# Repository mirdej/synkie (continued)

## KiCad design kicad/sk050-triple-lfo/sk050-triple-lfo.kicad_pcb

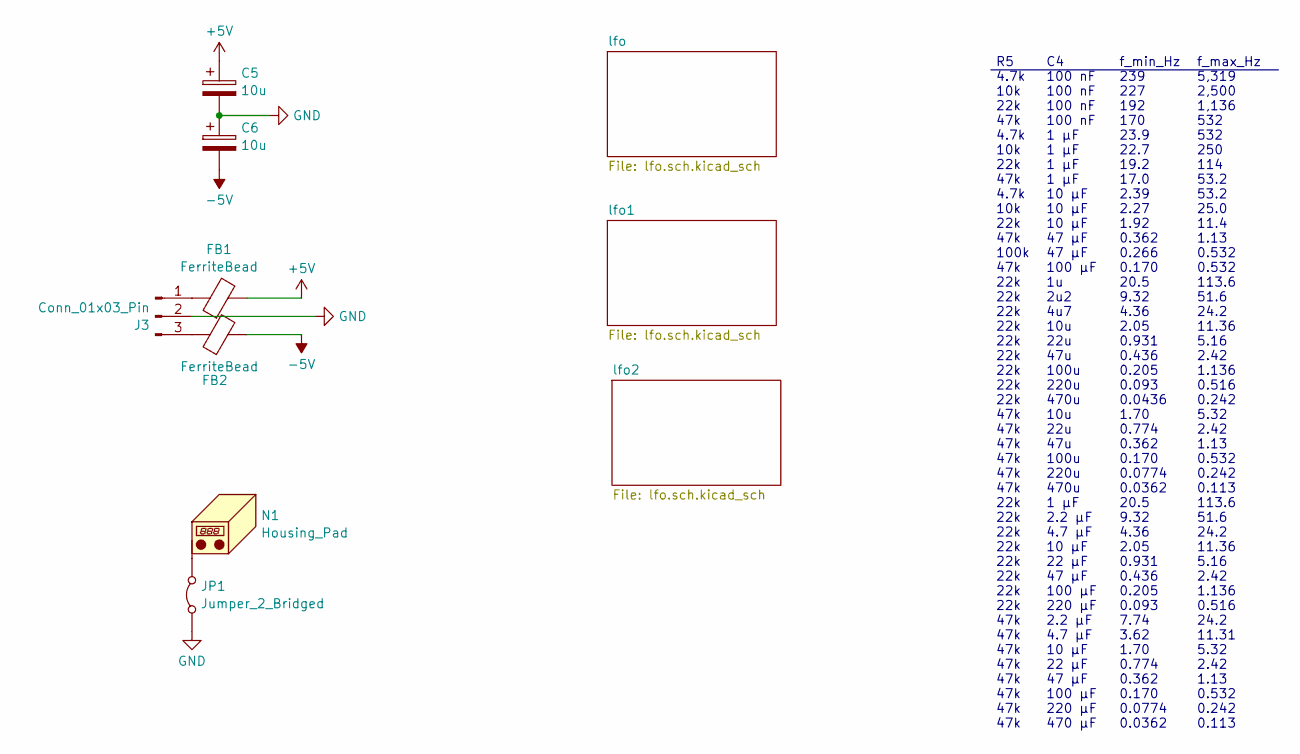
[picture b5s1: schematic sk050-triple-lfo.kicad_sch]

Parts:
C5, C6: 10u; C_0805_2012Metric; LCSC C15850
FB1, FB2: FerriteBead; L_0805_2012Metric_Pad1.15x1.40mm_HandSolder; LCSC C1017
J3: Conn_01x03_Pin; Molex_KK-254_AE-6410-03A_1x03_P2.54mm_Vertical_SMD
JP1: Jumper_2_Bridged; SolderJumper-2_P1.3mm_Bridged2Bar_Pad1.0x1.5mm
N1: Housing_Pad; Frontplate_20mm

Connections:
+5V: C5.1, FB1.2; also elsewhere on the board
-5V: C6.2, FB2.2; also elsewhere on the board
GND: C5.2, C6.1, J3.2, JP1.1 (A); also elsewhere on the board
unnamed: FB1.1, J3.1
unnamed: FB2.1, J3.3
unnamed: JP1.2 (B), N1.1 (PAD)

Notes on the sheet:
R5 4.7k 10k 22k 47k 4.7k 10k 22k 47k 4.7k 10k 22k 47k 100k 47k 22k 22k 22k 22k 22k 22k 22k 22k 22k 47k 47k 47k 47k 47k 47k 22k 22k 22k 22k 22k 22k 22k 22k 47k 47k 47k 47k 47k 47k 47k 47k
f_max_Hz 5,319 2,500 1,136 532 532 250 114 53.2 53.2 25.0 11.4 1.13 0.532 0.532 113.6 51.6 24.2 11.36 5.16 2.42 1.136 0.516 0.242 5.32 2.42 1.13 0.532 0.242 0.113 113.6 51.6 24.2 11.36 5.16 2.42 1.136 0.516 24.2 11.31 5.32 2.42 1.13 0.532 0.242 0.113
f_min_Hz 239 227 192 170 23.9 22.7 19.2 17.0 2.39 2.27 1.92 0.362 0.266 0.170 20.5 9.32 4.36 2.05 0.931 0.436 0.205 0.093 0.0436 1.70 0.774 0.362 0.170 0.0774 0.0362 20.5 9.32 4.36 2.05 0.931 0.436 0.205 0.093 7.74 3.62 1.70 0.774 0.362 0.170 0.0774 0.0362
C4 100 nF 100 nF 100 nF 100 nF 1 µF 1 µF 1 µF 1 µF 10 µF 10 µF 10 µF 47 µF 47 µF 100 µF 1u 2u2 4u7 10u 22u 47u 100u 220u 470u 10u 22u 47u 100u 220u 470u 1 µF 2.2 µF 4.7 µF 10 µF 22 µF 47 µF 100 µF 220 µF 2.2 µF 4.7 µF 10 µF 22 µF 47 µF 100 µF 220 µF 470 µF

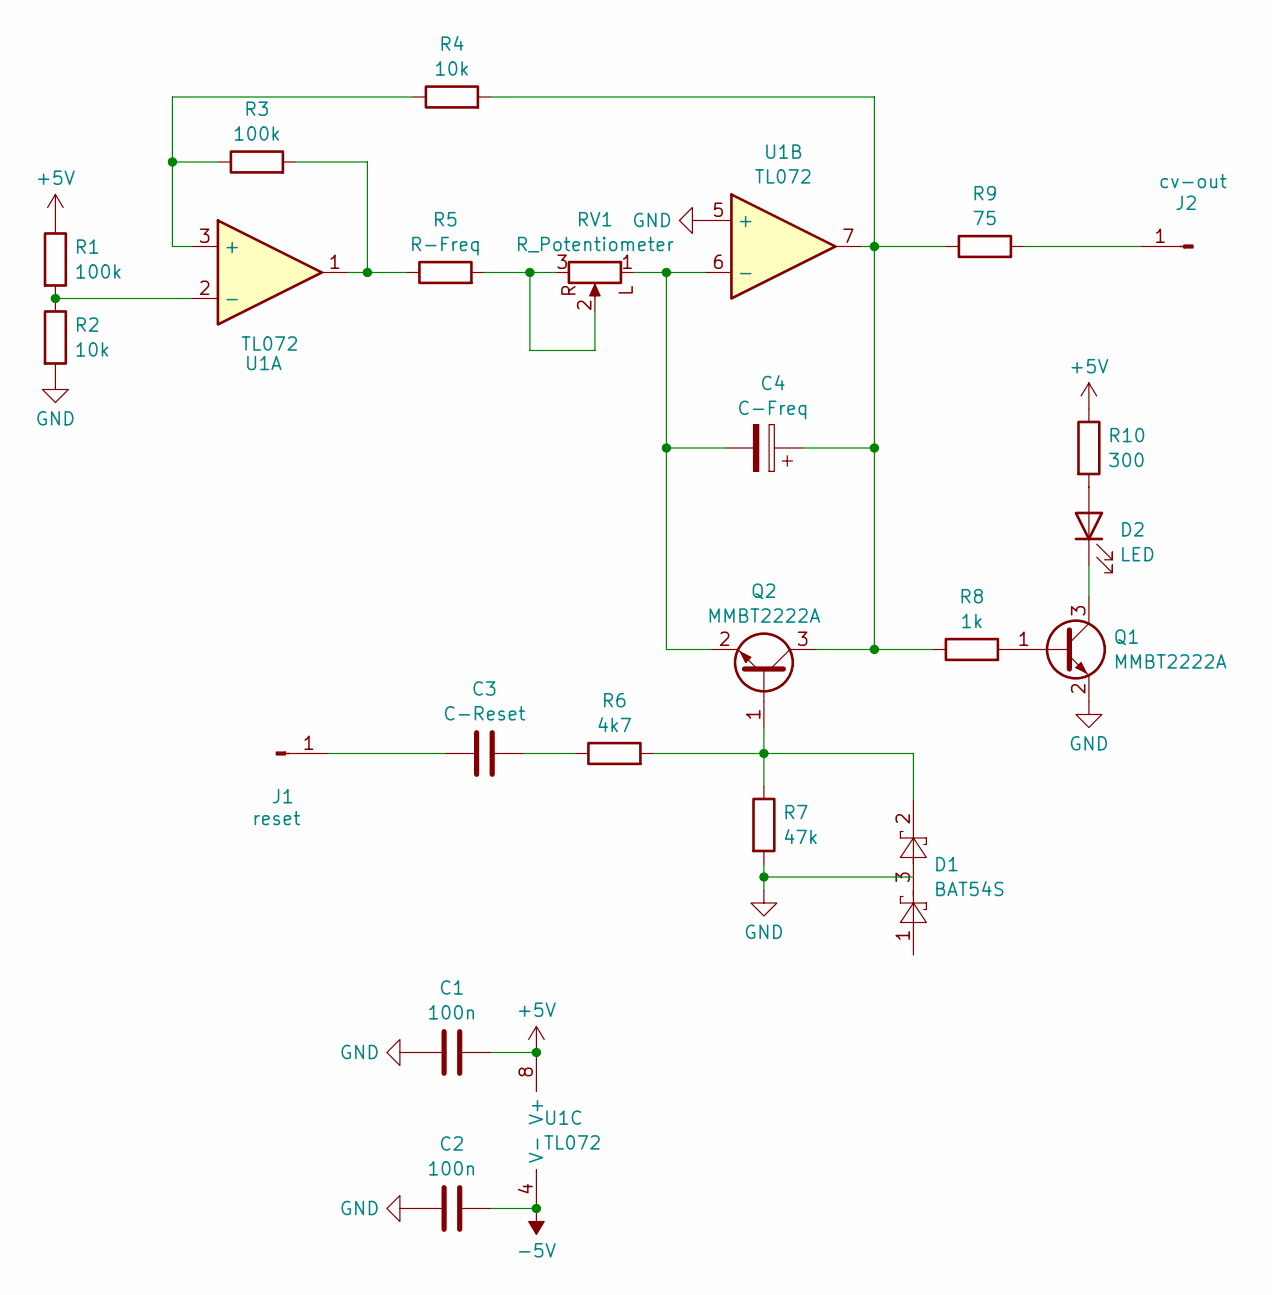
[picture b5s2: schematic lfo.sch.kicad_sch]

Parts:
C1, C2: 100n; C_0603_1608Metric; LCSC C14663
C3: C-Reset; C-Universal-0603-3528
C4: C-Freq; C-Universal-0603-3528
D1: BAT54S; SOT-23; LCSC C8592
D2: LED; LED_1206_3216Metric_ReverseMount_Hole1.8x2.4mm; LCSC C125108
J1: reset; Banana2mm-Löthülse
J2: cv-out; Banana2mm-Löthülse
Q1, Q2: MMBT2222A; SOT-23; LCSC C82460
R1, R3: 100k; R_0603_1608Metric; LCSC C25803
R2, R4: 10k; R_0603_1608Metric; LCSC C25804
R5: R-Freq; R_0805_2012Metric_Pad1.15x1.40mm_HandSolder
R6: 4k7; R_0603_1608Metric; LCSC C23162
R7: 47k; R_0603_1608Metric; LCSC C25819
R8: 1k; R_0603_1608Metric; LCSC C21190
R9: 75; R_0603_1608Metric; LCSC C4275
R10: 300; R_0603_1608Metric; LCSC C23025
RV1: R_Potentiometer; Potentiometer_Uwe_100k_frontplate
U1: TL072; SOIC-8_3.9x4.9mm_P1.27mm; LCSC C6961

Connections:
+5V: C1.2, R1.1, R10.1, U1.8 (V+); also elsewhere on the board
-5V: C2.2, U1.4 (V-); also elsewhere on the board
GND: C1.1, C2.1, D1.3, Q1.2 (E), R2.2, R7.2, U1.5 (+); also elsewhere on the board
unnamed: C3.1, R6.1
unnamed: D2.2 (A), R10.2
unnamed: D2.1 (K), Q1.3 (C)
unnamed: C3.2, J1.1
unnamed: J2.1, R9.2
unnamed: Q1.1 (B), R8.2
unnamed: D1.2, Q2.1 (B), R6.2, R7.1
unnamed: C4.1, Q2.3 (C), R4.2, R8.1, R9.1, U1.7
unnamed: C4.2, Q2.2 (E), RV1.1 (L), U1.6 (-)
unnamed: R3.2, R5.1, U1.1
unnamed: R5.2, RV1.2, RV1.3
unnamed: R3.1, R4.1, U1.3 (+)
unnamed: R1.2, R2.1, U1.2 (-)

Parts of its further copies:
C7, C8, C11, C12: 100n; C_0603_1608Metric; LCSC C14663
C9, C13: C-Reset; C-Universal-0603-3528
C10, C14: C-Freq; C-Universal-0603-3528
D3, D5: BAT54S; SOT-23; LCSC C8592
D4, D6: LED; LED_1206_3216Metric_ReverseMount_Hole1.8x2.4mm; LCSC C125108
J4, J6: reset; Banana2mm-Löthülse
J5, J7: cv-out; Banana2mm-Löthülse
Q3, Q4, Q5, Q6: MMBT2222A; SOT-23; LCSC C82460
R11, R13, R21, R23: 100k; R_0603_1608Metric; LCSC C25803
R12, R15, R22, R25: 10k; R_0603_1608Metric; LCSC C25804
R14, R24: R-Freq; R_0805_2012Metric_Pad1.15x1.40mm_HandSolder
R16, R26: 4k7; R_0603_1608Metric; LCSC C23162
R17, R27: 47k; R_0603_1608Metric; LCSC C25819
R18, R28: 1k; R_0603_1608Metric; LCSC C21190
R19, R29: 75; R_0603_1608Metric; LCSC C4275
R20, R30: 300; R_0603_1608Metric; LCSC C23025
RV2, RV3: R_Potentiometer; Potentiometer_Uwe_100k_frontplate
U2, U3: TL072; SOIC-8_3.9x4.9mm_P1.27mm; LCSC C6961

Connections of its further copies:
+5V: C7.2, C11.2, R11.1, R20.1, R21.1, R30.1, U2.8 (V+), U3.8 (V+); also elsewhere on the board
-5V: C8.2, C12.2, U2.4 (V-), U3.4 (V-); also elsewhere on the board
GND: C7.1, C8.1, C11.1, C12.1, D3.3, D5.3, Q4.2 (E), Q6.2 (E), R12.2, R17.2, R22.2, R27.2, U2.5 (+), U3.5 (+); also elsewhere on the board
unnamed: C9.1, R16.1
unnamed: C13.1, R26.1
unnamed: D4.2 (A), R20.2
unnamed: D4.1 (K), Q4.3 (C)
unnamed: D6.2 (A), R30.2
unnamed: D6.1 (K), Q6.3 (C)
unnamed: C9.2, J4.1
unnamed: J5.1, R19.2
unnamed: C13.2, J6.1
unnamed: J7.1, R29.2
unnamed: D3.2, Q3.1 (B), R16.2, R17.1
unnamed: C10.1, Q3.3 (C), R15.2, R18.1, R19.1, U2.7
unnamed: C10.2, Q3.2 (E), RV2.1 (L), U2.6 (-)
unnamed: Q4.1 (B), R18.2
unnamed: D5.2, Q5.1 (B), R26.2, R27.1
unnamed: C14.1, Q5.3 (C), R25.2, R28.1, R29.1, U3.7
unnamed: C14.2, Q5.2 (E), RV3.1 (L), U3.6 (-)
unnamed: Q6.1 (B), R28.2
unnamed: R13.2, R14.1, U2.1
unnamed: R14.2, RV2.2, RV2.3
unnamed: R23.2, R24.1, U3.1
unnamed: R24.2, RV3.2, RV3.3
unnamed: R13.1, R15.1, U2.3 (+)
unnamed: R11.2, R12.1, U2.2 (-)
unnamed: R23.1, R25.1, U3.3 (+)
unnamed: R21.2, R22.1, U3.2 (-)

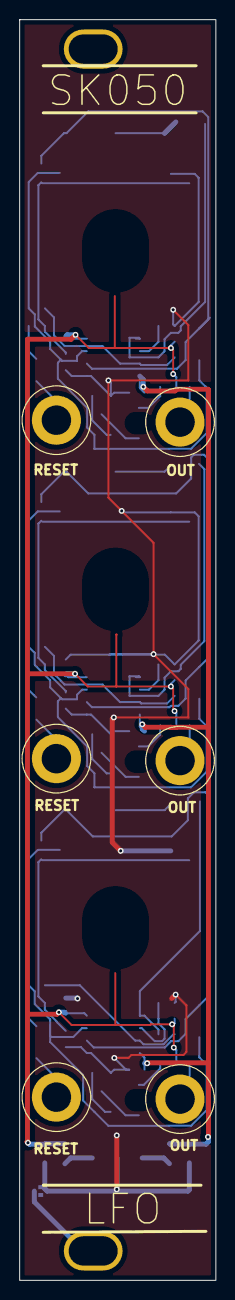
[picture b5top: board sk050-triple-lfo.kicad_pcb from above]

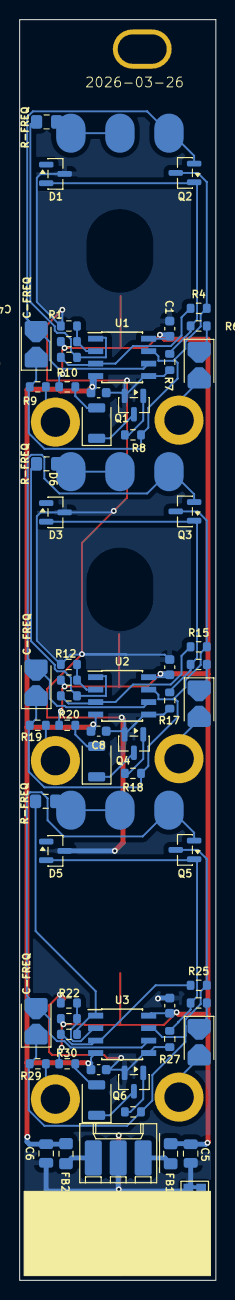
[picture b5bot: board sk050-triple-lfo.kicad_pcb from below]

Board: 2 copper layers, 20.0 x 128.5 mm, 73 parts (63 on the bottom side), 45 nets.

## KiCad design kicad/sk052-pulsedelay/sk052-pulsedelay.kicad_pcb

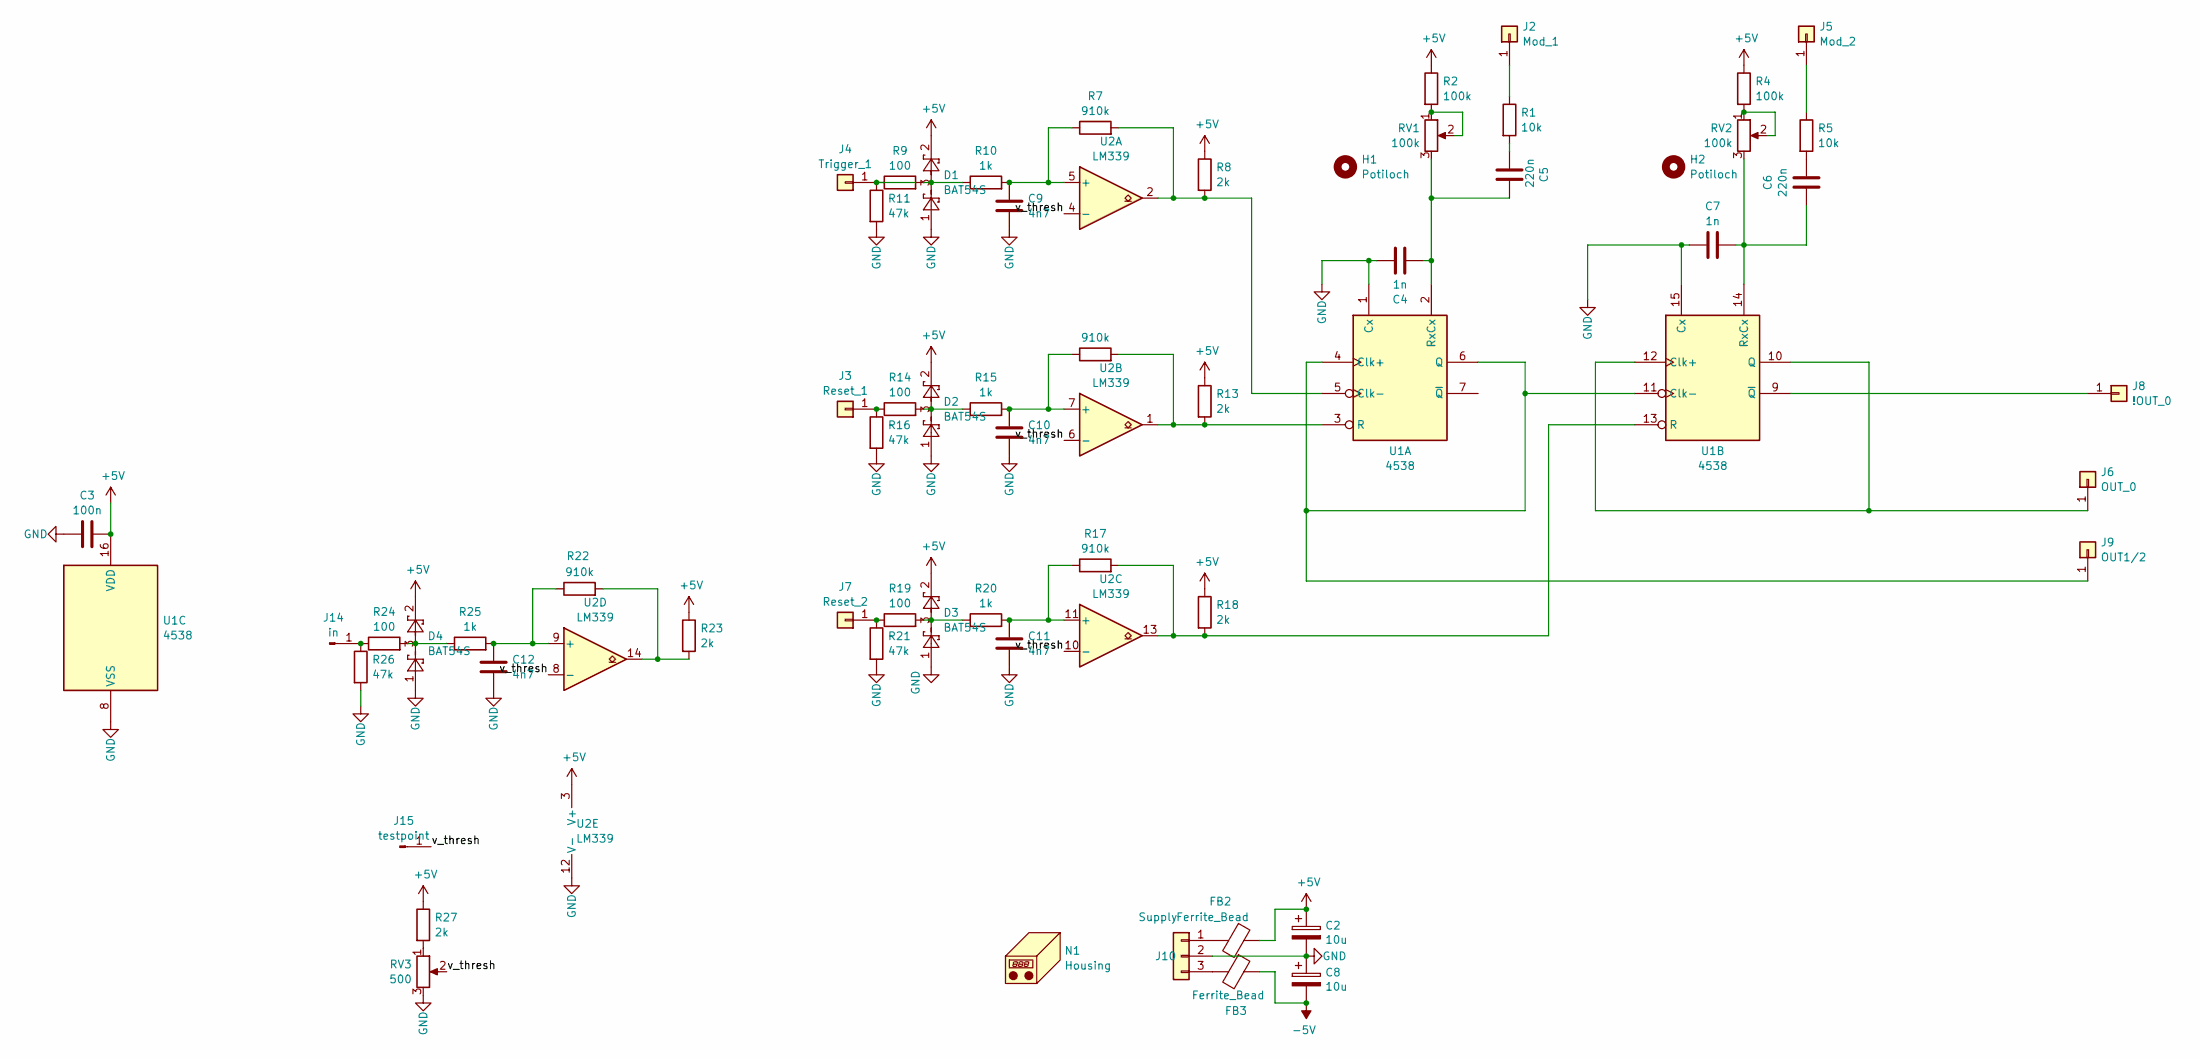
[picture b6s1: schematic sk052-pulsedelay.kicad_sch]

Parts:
C2, C8: 10u; CP_EIA-3528-21_Kemet-B
C3: 100n; R_0603_1608Metric_Pad1.05x0.95mm_HandSolder
C4, C7: 1n; R_0805_2012Metric_Pad1.15x1.40mm_HandSolder
C5, C6: 220n; R_0805_2012Metric_Pad1.15x1.40mm_HandSolder
C9, C10, C11, C12: 4n7; C_0805_2012Metric_Pad1.15x1.40mm_HandSolder
D1, D2, D3, D4: BAT54S; SOT-23
FB2, FB3: Ferrite_Bead; L_0805_2012Metric_Pad1.05x1.20mm_HandSolder
H1, H2: Potiloch; MountingHole_8.4mm_M8
J2: Mod_1; Solderpad-SYNKIEPAD-2mm
J3: Reset_1; Solderpad-SYNKIEPAD-2mm
J4: Trigger_1; Solderpad-SYNKIEPAD-2mm
J5: Mod_2; Solderpad-SYNKIEPAD-2mm
J6: OUT_0; Solderpad-SYNKIEPAD-2mm
J7: Reset_2; Solderpad-SYNKIEPAD-2mm
J8: !OUT_0; Solderpad-SYNKIEPAD-2mm
J9: OUT1/2; Solderpad-SYNKIEPAD-2mm
J10: Supply; smd-3pin
J14: in; Solderpad-SYNKIEPAD-2mm
J15: testpoint; TestPoint_Pad_D2.0mm
N1: Housing; Frontplate_30mm
R1, R5: 10k; R_0805_2012Metric_Pad1.15x1.40mm_HandSolder
R2, R4: 100k; R_0805_2012Metric_Pad1.15x1.40mm_HandSolder
R7, R12, R17, R22: 910k; R_0805_2012Metric_Pad1.15x1.40mm_HandSolder
R8, R13, R18, R23, R27: 2k; R_0805_2012Metric_Pad1.15x1.40mm_HandSolder
R9, R14, R19, R24: 100; R_0805_2012Metric_Pad1.15x1.40mm_HandSolder
R10, R15, R20, R25: 1k; R_0805_2012Metric_Pad1.15x1.40mm_HandSolder
R11, R16, R21, R26: 47k; R_0805_2012Metric_Pad1.15x1.40mm_HandSolder
RV1, RV2: 100k; Potentiometer_Uwe_100k_padsonly
RV3: 500; Potentiometer_Bourns_3224X_Vertical
U1: 4538; SOIC-16_3.9x9.9mm_P1.27mm
U2: LM339; SOIC-14_3.9x8.7mm_P1.27mm

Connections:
+5V: C2.1, C3.1, D1.2, D2.2, D3.2, D4.2, FB2.1, R2.1, R4.1, R8.1, R13.1, R18.1, R23.1, R27.1, U1.16 (VDD), U2.3 (V+)
-5V: C8.2, FB3.1
/v_thresh: J15.1, RV3.2, U2.4 (-), U2.6 (-), U2.8 (-), U2.10 (-)
GND: C2.2, C3.2, C4.1, C7.2, C8.1, C9.2, C10.2, C11.2, C12.2, D1.1, D2.1, D3.1, D4.1, J10.2, R11.2, R16.2, R21.2, R26.2, RV3.3, U1.1 (Cx), U1.8 (VSS), U1.15 (Cx), U2.12 (V-)
unnamed: C5.1, R1.2
unnamed: C6.1, R5.2
unnamed: D1.3, R9.2, R10.1
unnamed: D2.3, R14.2, R15.1
unnamed: D3.3, R19.2, R20.1
unnamed: D4.3, R24.2, R25.1
unnamed: J2.1, R1.1
unnamed: J3.1, R14.1, R16.1
unnamed: J4.1, R9.1, R11.1
unnamed: J5.1, R5.1
unnamed: J6.1, U1.10 (Q), U1.12 (Clk+)
unnamed: J7.1, R19.1, R21.1
unnamed: J8.1, U1.9 (~Q)
unnamed: J9.1, U1.4 (Clk+), U1.6 (Q), U1.11 (Clk-)
unnamed: FB2.2, J10.1
unnamed: FB3.2, J10.3
unnamed: J14.1, R24.1, R26.1
unnamed: R2.2, RV1.1, RV1.2
unnamed: R4.2, RV2.1, RV2.2
unnamed: R22.2, R23.2, U2.14
unnamed: R27.2, RV3.1
unnamed: R7.2, R8.2, U1.5 (Clk-), U2.2
unnamed: R12.2, R13.2, U1.3 (R), U2.1
unnamed: C4.2, C5.2, RV1.3, U1.2 (RxCx)
unnamed: R17.2, R18.2, U1.13 (R), U2.13
unnamed: C6.2, C7.1, RV2.3, U1.14 (RxCx)
unnamed: C9.1, R7.1, R10.2, U2.5 (+)
unnamed: C10.1, R12.1, R15.2, U2.7 (+)
unnamed: C11.1, R17.1, R20.2, U2.11 (+)
unnamed: C12.1, R22.1, R25.2, U2.9 (+)

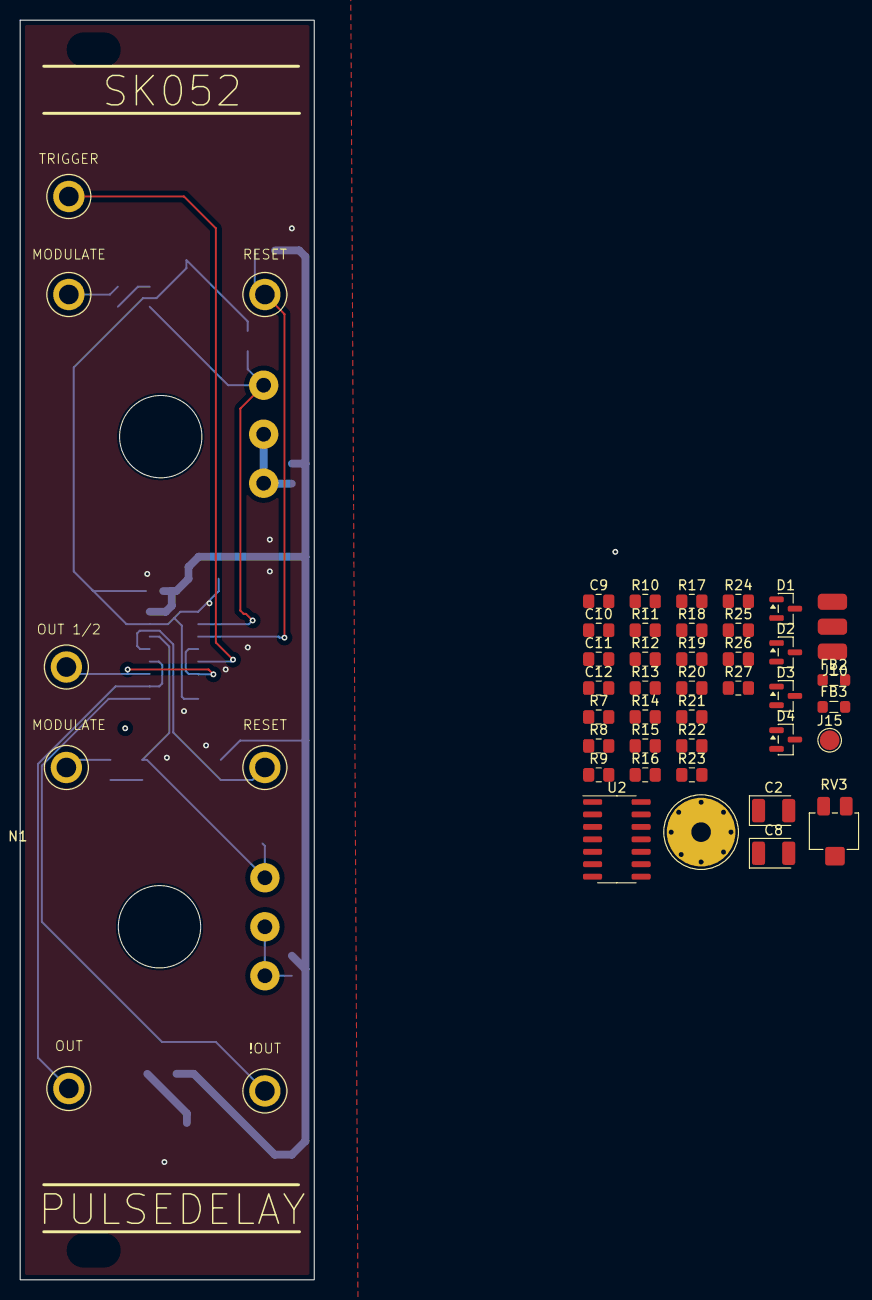
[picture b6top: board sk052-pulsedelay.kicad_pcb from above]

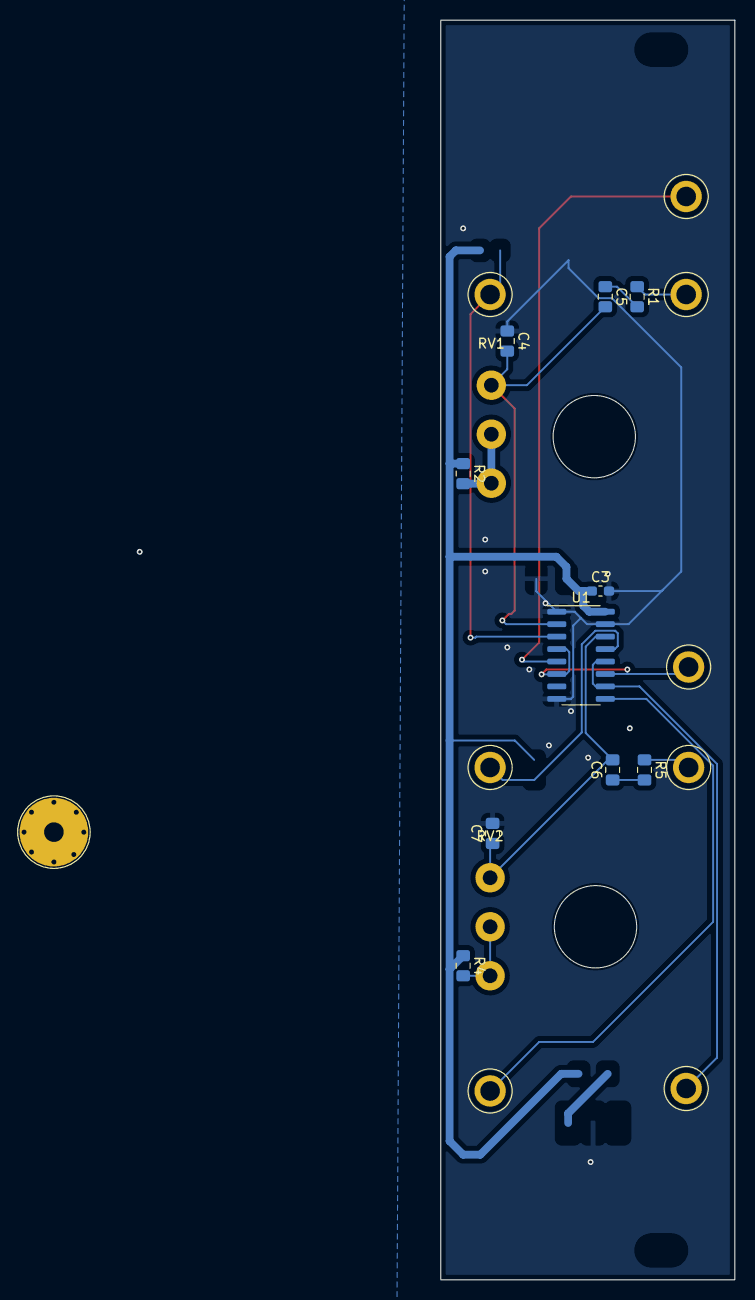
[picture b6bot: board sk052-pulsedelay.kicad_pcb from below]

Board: 2 copper layers, 30.0 x 128.5 mm, 61 parts (12 on the bottom side), 34 nets.

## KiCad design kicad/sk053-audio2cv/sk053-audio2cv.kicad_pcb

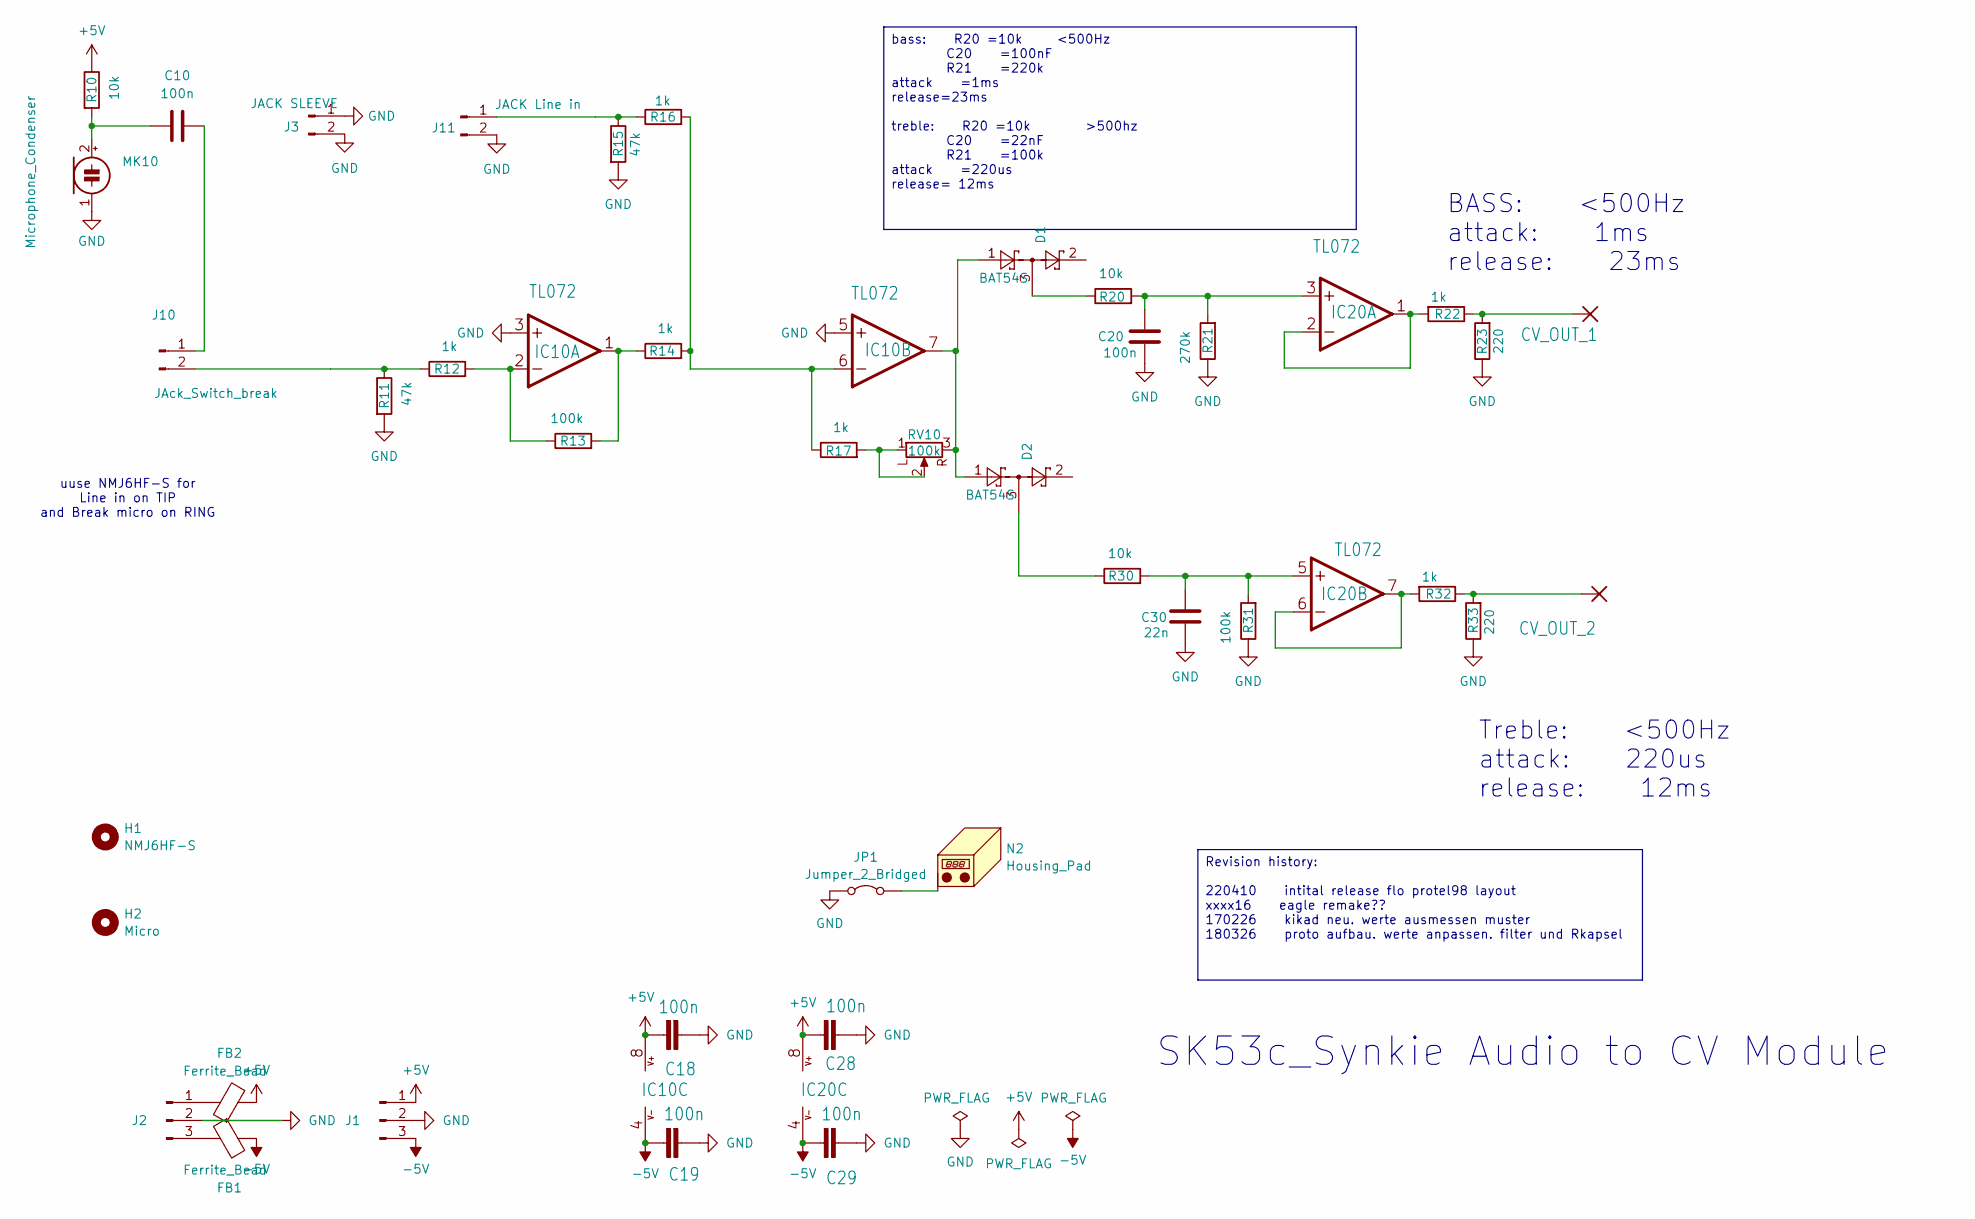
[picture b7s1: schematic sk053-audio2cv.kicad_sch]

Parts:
C10, C18, C19, C28, C29: 100n; C_0603_1608Metric
C20: 100n; C_0805_2012Metric
C30: 22n; C_0805_2012Metric
CV_OUT_1, CV_OUT_2: 3,17/1,1; Banana2mm-Löthülse
D1, D2: BAT54S; SOT-23
FB1, FB2: Ferrite_Bead; L_0805_2012Metric_Pad1.15x1.40mm_HandSolder; LCSC C1017
H1: NMJ6HF-S; NMJ6HF-S-Panelmount
H2: Micro; MountingHole_6mm
IC10, IC20: TL072; SOIC-8_3.9x4.9mm_P1.27mm
J1, J2: Conn_01x03_Pin; Molex_KK-254_AE-6410-03A_1x03_P2.54mm_Vertical_SMD
J3: JACK SLEEVE; smd-2pin
J10: JAck_Switch_break; smd-2pin
J11: JACK Line in; smd-2pin
JP1: Jumper_2_Bridged; SolderJumper-2_P1.3mm_Bridged2Bar_Pad1.0x1.5mm
MK10: Microphone_Condenser; smd-2pin
N2: Housing_Pad; Frontplate_20mm
R10, R20, R30: 10k; R_0805_2012Metric_Pad1.15x1.40mm_HandSolder
R11, R15: 47k; R_0805_2012Metric_Pad1.15x1.40mm_HandSolder
R12, R14, R16, R17, R22, R32: 1k; R_0805_2012Metric_Pad1.15x1.40mm_HandSolder
R13, R31: 100k; R_0805_2012Metric_Pad1.15x1.40mm_HandSolder
R21: 270k; R_0805_2012Metric_Pad1.15x1.40mm_HandSolder
R23, R33: 220; R_0805_2012Metric_Pad1.15x1.40mm_HandSolder
RV10: 100k; Potentiometer_Uwe_100k_frontplate

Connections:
+5V: C18.2, C28.2, FB2.2, IC10.8 (V+), IC20.8 (V+), J1.1, R10.1
-5V: C19.2, C29.2, FB1.2, IC10.4 (V-), IC20.4 (V-), J1.3
GND: C18.1, C19.1, C20.1, C28.1, C29.1, C30.1, IC10.3 (+IN), IC10.5 (+IN), J1.2, J2.2, J3.1, J3.2, J11.2, JP1.1 (A), MK10.1 (-), R11.2, R15.2, R21.1, R23.1, R31.1, R33.1
unnamed: CV_OUT_1.1, R22.1, R23.2
unnamed: CV_OUT_2.1, R32.1, R33.2
unnamed: D1.3, R20.1
unnamed: D2.3, R30.1
unnamed: IC10.2 (-IN), R12.2, R13.1
unnamed: IC10.1 (OUT), R13.2, R14.1
unnamed: IC10.6 (-IN), R14.2, R16.2, R17.1
unnamed: D1.1, D2.1, IC10.7 (OUT), RV10.3
unnamed: C20.2, IC20.3 (+IN), R20.2, R21.2
unnamed: IC20.1 (OUT), IC20.2 (-IN), R22.2
unnamed: C30.2, IC20.5 (+IN), R30.2, R31.2
unnamed: IC20.6 (-IN), IC20.7 (OUT), R32.2
unnamed: FB2.1, J2.1
unnamed: FB1.1, J2.3
unnamed: C10.2, J10.1
unnamed: J10.2, R11.1, R12.1
unnamed: J11.1, R15.1, R16.1
unnamed: JP1.2 (B), N2.1 (PAD)
unnamed: C10.1, MK10.2 (+), R10.2
unnamed: R17.2, RV10.1 (L), RV10.2

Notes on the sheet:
BASS: <500Hz attack: 1ms release: 23ms
Treble: <500Hz attack: 220us release: 12ms
SK53c_Synkie Audio to CV Module
uuse NMJ6HF-S for Line in on TIP and Break micro on RING
Revision history: 220410 intital release flo protel98 layout xxxx16 eagle remake?? 170226 kikad neu. werte ausmessen muster 180326 proto aufbau. werte anpassen. filter und Rkapsel
bass: R20 =10k <500Hz C20 =100nF R21 =220k attack =1ms release=23ms treble: R20 =10k >500hz C20 =22nF R21 =100k attack =220us release= 12ms

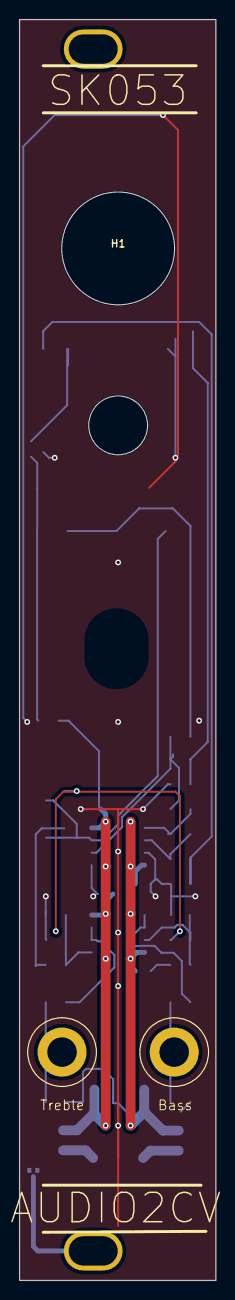
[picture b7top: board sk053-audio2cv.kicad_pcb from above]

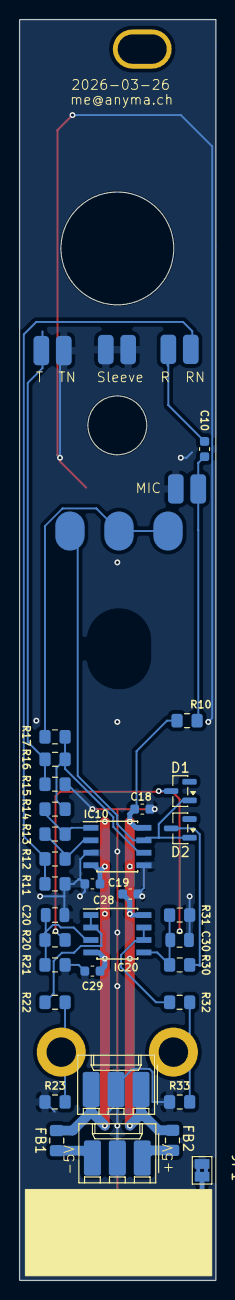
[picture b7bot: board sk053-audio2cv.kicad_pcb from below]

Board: 2 copper layers, 20.0 x 128.5 mm, 42 parts (36 on the bottom side), 23 nets.
